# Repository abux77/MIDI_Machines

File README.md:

# MIDI Machines

Two independent MIDI random-loop sequencers inspired by Music Thing Modular's
Turing Machine, using the MIDI Grids Raspberry Pi Pico hardware. Firmware and
browser compile the same C engine; the webpage uses WebAssembly and includes a
looped sample synth. The Pico plays the same four waveforms through its PCM5102A
audio output.

## Controls

| Existing knob | MIDI Machines |
|---|---|
| BD | Machine 1 mutation / lock |
| X | Machine 1 length |
| SD | Machine 2 mutation / lock |
| Y | Machine 2 length |
| HH | Shared pitch range, 1–48 semitones |
| Chaos | Shared scale |
| Tempo | 40–240 BPM; quarter / half / full speed with external clock |

Clockwise locks stored steps, the centre randomizes them, and anticlockwise
inverts each stored step on successive passes for a loop twice the selected length. Endpoint dead zones make
locking reliable on physical pots. Length choices are every integer from 0 to 16. Zero mutes that machine and
pauses its register, preserving the loop until a nonzero length is selected.
Each machine keeps a bank of 16 stored step values; the low eight bits of each
value determine pitch. Length selects the first 0–16 steps without overwriting
the hidden steps. Mutation changes played steps; hidden steps remain intact.
Start resets playheads while retaining register contents, so locked material is
preserved. Stop silences notes. Each machine advances every six MIDI clocks
(one sixteenth note), with velocity 100 and approximately 80% gate length.

Scales: chromatic, major, natural minor, Dorian, Mixolydian, major pentatonic,
minor pentatonic, harmonic minor, whole tone. Quantization chooses the nearest
scale tone, preferring the lower note on ties, and stays within MIDI 0–127.

## Browser

[Play MIDI Machines online](https://abux77.github.io/MIDI_Machines/).

```sh
python3 -m http.server 8000 --directory web --bind 127.0.0.1
```

Open http://localhost:8000 and click Start. The checked-in `web/machines.wasm`
is ready to use. Controls and voice settings persist in browser local storage.
Choose MIDI input/output under **Settings**. Web MIDI requires
a supporting browser such as Chromium and HTTPS or localhost. Browser sound is
optional. Enable **Clock & transport only** in Settings to follow MIDI Clock,
Start, Stop and Continue while ignoring all incoming note and CC messages. This
filter is saved in this browser and does not affect local controls or MIDI output. Stop and hidden-tab handling release notes and stop playback.

For a silent hardware screen, enable **Use as hardware screen**, select the Pico
input, then stop/start the hardware. The screen receives full-resolution knob
CCs, clock and actual played MIDI notes. Register visualization is local to the
browser instrument: hardware register state is not transferred. Set webpage
channels to match the hardware so actual notes appear under the correct machine.
Avoid routing the output back into the input.

## Firmware and serial BOOTSEL

Flash `build/midi_machines.uf2` to the original RP2040 Pico's RPI-RP2 drive.
For initial installation, hold the Pico BOOTSEL button while connecting USB.
Subsequent updates can enter the bootloader through the USB CDC serial port:

```text
bootsel
```

Send the command followed by Enter (115200 baud is fine). Firmware stops playback,
sends note-offs and Stop, flushes serial/MIDI queues for 100 ms, then calls
`reset_usb_boot(0, 0)`. RPI-RP2 appears. This command is refused while the
configuration drive is mounted; safely eject it first. `status` reports clock,
knobs, registers and voice settings; `test` sends a short Machine 1 root note.
The inherited `format` command erases the reserved storage partition and restores
factory files; normal firmware updates preserve that partition.

## Hardware configuration

Hold Start/Stop while powering on to expose the reserved 1 MiB USB drive.
Replace `CONFIG.TXT` and safely eject. The unit reloads settings while stopped.
The webpage's **Download CONFIG.TXT** exports its root/octave/channel settings;
copy that file onto the hardware drive to apply them. Webpage settings do not
write hardware flash over MIDI.

```text
LIBRARY,2
USB_MIDI,ON
TM1,CH1,ROOT0,OCT3,SOUND1
TM2,CH2,ROOT0,OCT3,SOUND2
```

Channels: 1–16. ROOT: 0–11 (C–B). OCT: 0–8, where MIDI base note is
`12 * OCT + ROOT`; OCT3/ROOT0 is MIDI 36 (usually named C2). Browser note labels
use MIDI 60 = C4. Invalid settings retain defaults; legacy BD/SD/HH entries do
not configure the machines. `USB_MIDI,OFF` disables USB MIDI after reboot;
DIN and CDC remain available. Full-line `#` comments are supported.

Hardware pinout is unchanged: UART0 MIDI GP0/GP1; LEDs GP6–GP9; Start/Stop GP10;
PCM5102A GP11–GP13; mux select GP16–GP19, ADC GP26.
The first DIN/USB realtime source owns external sync. Start resets phase,
Continue retains it, Stop silences notes. Clock alone does not start playback.
After two seconds without clock, running playback resumes internally. Outgoing
external MIDI clock retains its original rate despite tempo-knob division.

CCs retain the original hardware assignments on MIDI channel 1: X/length1=20,
Y/length2=21, BD/mutation1=22, SD/mutation2=23, HH/range=24, Chaos/scale=25,
tempo=26. Fine CCs are coarse+32; CC27 reports effective division 1/2/4.

## Build and verify

With Pico SDK 2.2.0 (TinyUSB initialized), Arm GNU 14.2.Rel1, CMake and Make/Ninja:

```sh
cmake -S . -B build -DPICO_BOARD=pico -DPICO_SDK_PATH=/path/to/pico-sdk
cmake --build build -j4
```

With Clang and lld (or WASI SDK 34):

```sh
WASM_CC=/path/to/wasi-sdk/bin/clang python3 tools/build_web.py
sh tools/test.sh
python3 tests/test_web.py
```

Tests cover both lock endpoints, loop lengths, quantization, deterministic RNG,
clock divisions, storage settings, full-resolution MIDI controls, browser synth,
silent hardware screen, and native/WebAssembly event, pitch and register parity.
Bench verification remains necessary: see [hardware checks](docs/HARDWARE_VALIDATION.md).

`core/turing.c` and `core/machines_sequencer.c` are shared by both platforms.
`src/main.c` owns Pico I/O; `web/bridge.c` exposes the C engine to the browser;
`web/app.js` handles UI, scheduling, MIDI and synthesis. Inherited Grids engine,
sample storage and associated tests remain for reference and future audio work;
they do not generate the new sequencer's notes.

This project derives from [MIDI Grids](https://github.com/abux77/MIDI_Grids).
Turing behavior is inspired by [Music Thing Modular](https://www.musicthing.co.uk/Turing-Machine/).
See [LICENSE.md](LICENSE.md) for inherited licensing and attribution.

## Sounds and hardware editor

The active palette is Bass, Gritty wide bass, Gritty 808 bass, Prophet wobble note,
and Prophet wobbling key, in that order (SOUND1–SOUND5). Only Bass loops. The other
four sounds play complete tuned recordings; a new note retriggers that machine's
voice on the Pico. Stop silences all voices. The browser can overlap recordings.

Browser recordings remain stereo at 44.1 kHz. Pico recordings are complete mono
PCM16 at 22.05 kHz, interpolated into the existing 44.1 kHz stereo I²S stream.
`tools/embed_hardware_synth.py` generates their flash tables from the tuned web
assets. This firmware includes only three legacy factory drum files to leave
space for the synth library. Existing files in the editable partition are retained.
The four original CC0 waveforms remain archived in `samples/synth/`; user recordings
have separate provenance and are not covered by that CC0 license.

In the webpage, choose the Pico MIDI input, click **Read hardware**, edit each
machine's Sound, Root, Octave, MIDI channel, Note mask and Mask variation, then
click **Apply to hardware**. Subdivision applies to both machines. The editor
uses a dedicated Pico output, independent of the musical MIDI output selector.
A protocol/palette handshake is required before Apply is enabled. Updates apply
in RAM and do not write flash while playing. They reset on reboot.

To save across reboots, click **Download CONFIG.TXT**, copy it to the hardware's
configuration drive, and safely eject. The exported format is:

```text
LIBRARY,2
USB_MIDI,ON
SUBDIV,16
MASK1,100,0
MASK2,100,0
TM1,CH1,ROOT0,OCT3,SOUND1
TM2,CH2,ROOT0,OCT3,SOUND2
```

MASK lines contain play density (0–100) and variation (0–63); the C firmware and
browser use the same fixed pattern bank and rotations. LIBRARY,2 identifies the
five-sound menu. Old configurations without that marker preserve Bass selections
and replace removed starter sounds with the per-machine defaults.

Editor protocol v1 uses channel 16 CC80–92 for two sets of root/octave/channel/
sound/mask/variation and global subdivision. Channel and sound are zero based.
CC119=1 requests state, 3 starts an update, and 2 commits all thirteen validated
fields together. Replies begin CC119=77, include CC116=1 and CC117=2, send the
thirteen fields, and end CC119=78. Replies are USB only. This is a private protocol
for the Pico, not a general MIDI-controller assignment.

`tools/bin_to_uf2.py build/midi_machines.bin build/midi_machines.uf2` wraps a linked
RP2040 binary when picotool is unavailable. It rejects images larger than 1 MiB;
the linker independently enforces the editable volume's boundary.

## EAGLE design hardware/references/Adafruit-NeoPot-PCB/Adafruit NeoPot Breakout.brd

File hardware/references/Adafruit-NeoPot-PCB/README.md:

## Adafruit NeoPot - Clear Shaft Potentiometer with RGB NeoPixel PCB

<a href="http://www.adafruit.com/products/6387"><br/>
Click here to purchase one from the Adafruit shop</a>

PCB files for the Adafruit NeoPot - Clear Shaft Potentiometer with RGB NeoPixel. 

Format is EagleCAD schematic and board layout
* https://www.adafruit.com/product/6387

### Description

Clear Shaft Potentiometer with RGB NeoPixel

### License

Adafruit invests time and resources providing this open source design, please support Adafruit and open-source hardware by purchasing products from [Adafruit](https://www.adafruit.com)!

Designed by Limor Fried/Ladyada for Adafruit Industries.

Creative Commons Attribution/Share-Alike, all text above must be included in any redistribution. 
See license.txt for additional details.

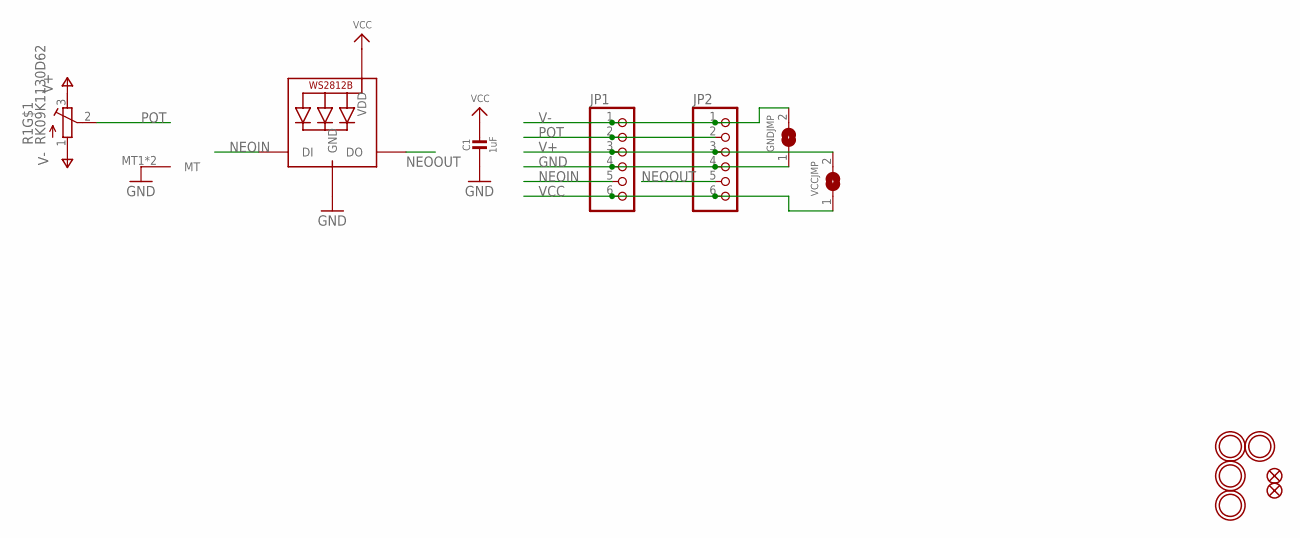
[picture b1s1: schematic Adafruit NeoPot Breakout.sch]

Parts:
C1: 1uF; 0603-NO
FID1, FID2: FIDUCIAL_0.5MM
GNDJMP: SOLDERJUMPER; SOLDERJUMPER_ARROW_NOPASTE
JP1, JP2: HEADER-1X676MIL; 1X06_ROUND_76
LED1: SK6812-3535; SK6812_2020
R1: RK09K1130D62; POT_RK09
U$2, U$3, U$4, U$5: MOUNTINGHOLE2.5; MOUNTINGHOLE_2.5_PLATED
VCCJMP: SOLDERJUMPER; SOLDERJUMPER_ARROW_NOPASTE

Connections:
GND: C1.2, GNDJMP.1, JP1.4, JP2.4, LED1.3 (GND), R1.MT1 (MT), R1.MT2 (MT)
NEOIN: JP1.5, LED1.4 (DI)
NEOOUT: JP2.5, LED1.2 (DO)
POT: JP1.2, JP2.2, R1.2 (S)
V+: JP1.3, JP2.3, R1.3 (E), VCCJMP.2
V-: GNDJMP.2, JP1.1, JP2.1, R1.1 (A)
VCC: C1.1, JP1.6, JP2.6, LED1.1 (VDD), VCCJMP.1

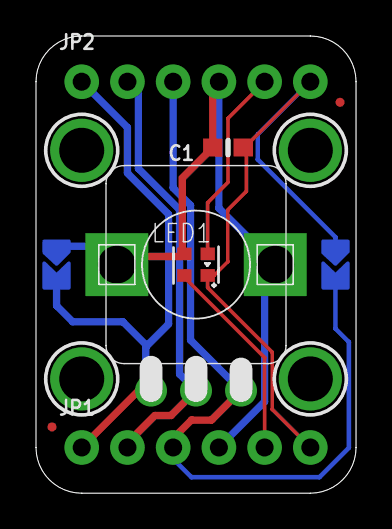
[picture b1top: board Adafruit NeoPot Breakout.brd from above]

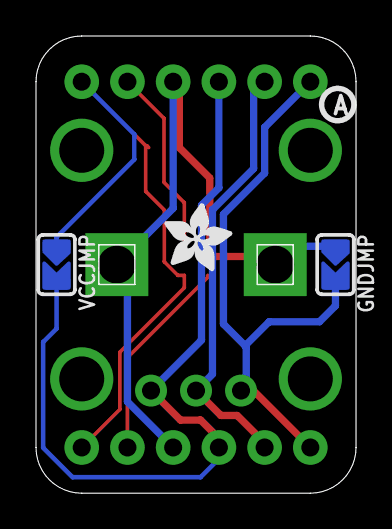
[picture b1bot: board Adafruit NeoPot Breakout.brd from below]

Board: 2 copper layers, 17.8 x 25.4 mm, 35 parts (10 on the bottom side), 7 nets.

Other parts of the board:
PLABEL0: PLABEL0
PLABEL1: PLABEL1
PLABEL2: PLABEL2
PLABEL3: PLABEL3
PLABEL4: PLABEL4
PLABEL5: PLABEL5
PLABEL6: PLABEL6
PLABEL7: PLABEL7
PLABEL8: PLABEL8
PLABEL9: PLABEL9
PLABEL10: PLABEL10
PLABEL11: PLABEL11
PLABEL12: PLABEL12
PLABEL13: PLABEL13
PLABEL14: PLABEL14
PLABEL15: PLABEL15
PLABEL16: PLABEL16
PLABEL17: PLABEL17
PLABEL18: PLABEL18
PLABEL19: PLABEL19
U$6: PCBFEAT-REV-040
U$7: ADAFRUIT_3.5MM

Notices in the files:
parts and their libraries:
microbuilder: This work is placed in the public domain, and may be freely used for commercial and non-commercial work with the following conditions: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
